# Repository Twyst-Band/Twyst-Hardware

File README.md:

# Twyst — Intelligent Motion Tracking & Exercise Feedback System

## Overview

Twyst is a wearable motion analysis system that integrates sensor-embedded bandanas with an intuitive mobile application to monitor, evaluate, and improve human movement. Designed for sports, fitness, rehabilitation, and physical therapy, Twyst provides real-time feedback on exercise execution accuracy using advanced motion analysis and AI-based comparison algorithms.

Developed by students from the National College of Computer Science “Grigore Moisil” Brașov, Twyst combines embedded engineering, data science, and mobile app design to create a seamless hardware-software ecosystem that makes motion tracking accessible and engaging.
 
## Objectives

Twyst aims to:
- Provide precise motion analysis using distributed wearable sensors.
- Deliver live, data-driven feedback for form correction and performance improvement.
- Develop a machine-learning framework that learns from professionals and guides beginners.
- Support medical rehabilitation by tracking therapeutic exercises and preventing re-injury.
- Offer a comfortable, modular, and scalable hardware system adaptable to various body types and activities.

Key operational goals include:
- <2° RMS error in orientation estimation.
- 95% exercise recognition accuracy.
- Real-time posture correction feedback.
- 8+ hours battery life and automatic calibration.

## How It Works

The system operates in two main phases:
1.	Training Phase – A professional user performs multiple repetitions of an exercise wearing several Twyst bandanas. The algorithm identifies the most relevant sensors and stores their motion data as a reference.
2.	User Phase – A beginner attaches bandanas to the same body parts and performs the exercise. Twyst compares their movement to the reference model, scoring accuracy and providing corrective suggestions.

Twyst uses sensor fusion (Kalman filters) to combine gyroscope, accelerometer, and magnetometer data. Movement analysis and comparison are based on Principal Component Analysis (PCA) for segmentation and Bézier curve modeling for motion representation, ensuring precise yet efficient feedback.

## Related Work

Twyst draws inspiration from several existing systems:
- SlimeVR: Open-source IMU-based full-body tracker for VR; lacks exercise integration and suffers from drift.
- OptiTrack: High-precision optical tracking used in professional environments; too costly and complex for personal use.
- Oculus Insight: Inside-out tracking with 6DoF accuracy; limited to upper-body movement and headset constraints.

Twyst bridges the gap — delivering OptiTrack-like accuracy with SlimeVR’s affordability and Oculus’ simplicity, optimized for fitness and rehabilitation.

## Software Architecture

Mobile Application
- Built in SwiftUI (iOS), with an Android version in development.
- Features include:
- Exercise browsing and categorization.
- Live activity tracking and performance analytics.
- Gamified UI inspired by Duolingo, featuring progress visualization, rewards, and motivational feedback.
- Mascot: Twy — a friendly athletic fox serving as a motivational guide and branding symbol.

Embedded Software
- Runs on ESP32-C3 using the Arduino framework (C).
- Handles sensor communication (SPI/I²C), data fusion, calibration, and Bluetooth data transfer.
- Implements local Kalman filtering before aggregating data to the main bandana and mobile app for analysis.

## Hardware Design

Bandana Types
- Main Bandana: Acts as the master node; equipped with a touchscreen, pulse oximeter, and temperature sensor.
- Secondary Bandanas: Smaller, lightweight, and communicate with the main unit via UWB and Bluetooth.

## Components

Component	Model / Description
Microcontroller	ESP32-C3
IMU	MPU9250
UWB Module	Ai-Thinker BU03 DW3000
Display	Waveshare Round TFT (GC9A01 driver)
Pulse Oximeter	GY-MAX30100
Temperature Sensor	MF52
Battery	Li-Po with Boost Regulator HW626
Material	PETG 3D-printed enclosures, nylon straps

## Electronics & Prototyping
- Designed using KiCad for PCB schematics.
- 3D-printed casings optimized for comfort and modular assembly.
- Built for durability, skin safety, and easy debugging.

## Business Model

Twyst’s business strategy focuses on:
- Selling hardware kits (bandanas + mobile app).
- Generating secondary revenue from anonymized motion data used in research, medicine, and biomechanics.
- Promoting accessibility and personalization to encourage wide adoption across fitness, rehabilitation, and research markets.

Business Plan
Research Paper

## Research & Algorithms

Twyst’s research focuses on mathematical modeling for accurate motion comparison:
- Sensor Model: Quaternion-based orientation estimation via Kalman filtering.
- Segmentation: PCA identifies repetitions and removes noise.
- Motion Representation: Bézier curves smooth motion data for scalable comparison.
- Evaluation Metrics: Curve distance, amplitude, and phase alignment define feedback precision.

These techniques ensure low drift, real-time responsiveness, and robust cross-user comparison.

## License

This project is currently in research and prototype stage under educational use. Future licensing will be determined upon commercial release.
 presentation)?

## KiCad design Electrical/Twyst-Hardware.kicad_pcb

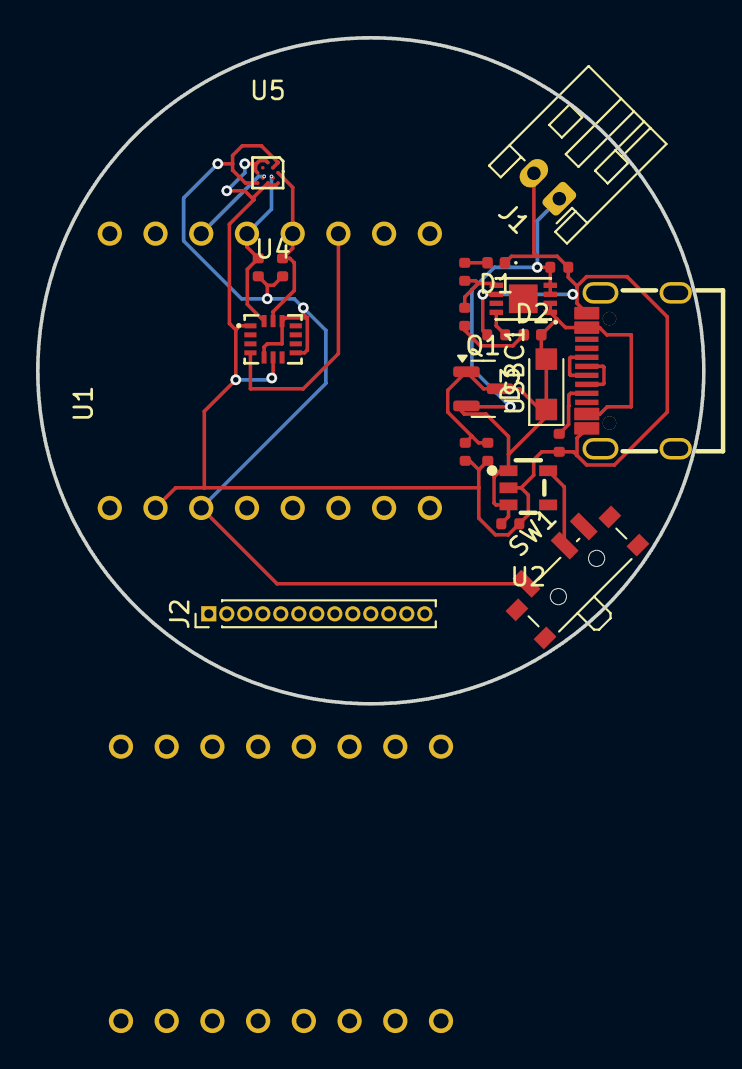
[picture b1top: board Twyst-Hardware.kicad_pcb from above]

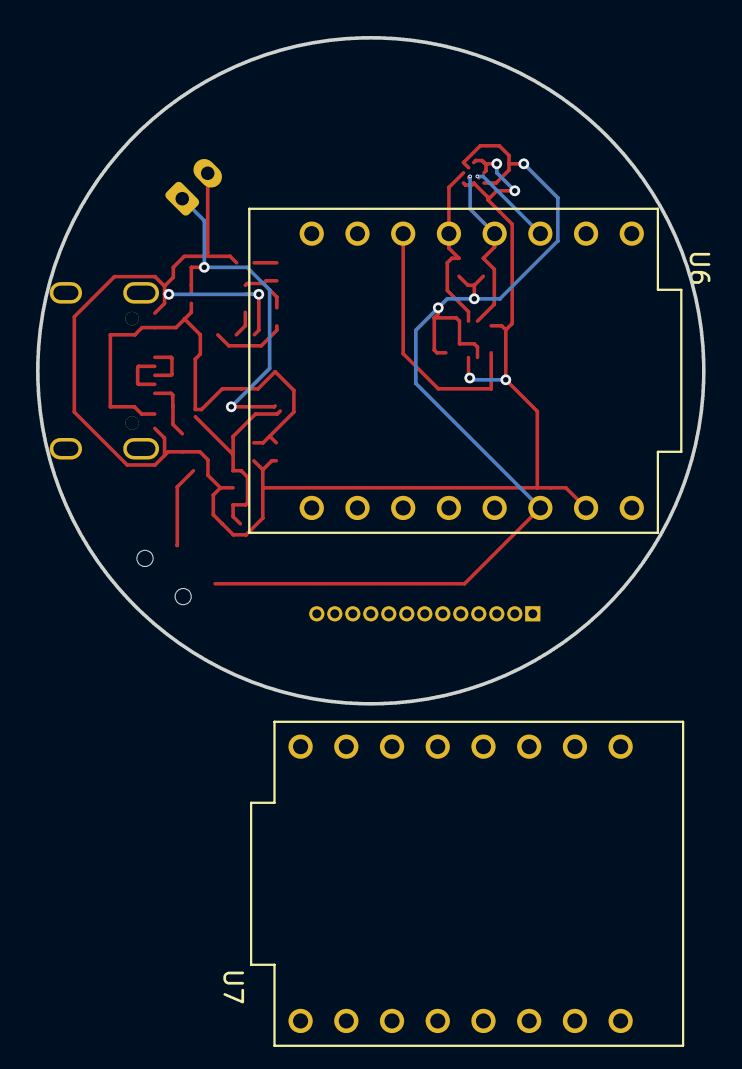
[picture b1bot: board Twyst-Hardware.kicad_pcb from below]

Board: 2 copper layers, 37.0 x 37.0 mm, 24 parts (2 on the bottom side), 17 nets.

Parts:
C1, C2, C3: 10µF; C_0402
D1, D2: LED; LED_0402_1005Metric
D3: PMEG4020ER; Nexperia_CFP3_SOD-123W
J1: Conn_01x02_Pin; JST_PH_S2B-PH-K_1x02_P2.00mm_Horizontal
J2: Conn_01x13_Pin; PinHeader_1x13_P1.00mm_Vertical
Q1: BSS84; SOT-23
R1: 5.1kΩ; R_0402
R2: 2kΩ; R_0402
R3, R4: 1kΩ; R_0402
R5: 100kΩ; R_0402
R6, R7: 4.7kΩ; R_0402
SW1: SW_SPDT; SW_SPDT_PCM12
U1: MCP73831-2ACI/MC; TDFN-8_L3.0-W2.0-P0.50-BL-EP1.6
U2: AP2112K-3.3TRG1_C23380830; SOT-23-5_L2.9-W1.6-P0.95-LS2.8-BR
U4: ICM-45686; LGA-14_L3.0-W2.5-P0.50-TL
U5: BMM150; WLCSP-12_L1.6-W1.6_BMM150
U6, U7: ESP32-C3_SUPERMINI_TH; MODULE_ESP32-C3_SUPERMINI_TH
USBC1: TYPE-C-31-M-12; USB-C_SMD-TYPE-C-31-M-12_1

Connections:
+3.3V: R6.1, R7.1, SW1.1 (A), U4.5 (VDDIO), U4.8 (VDD), U4.12 (AP_CS), U5.A1 (PS), U5.B2 (VDDIO), U5.E5 (VDD), U6.3.3 (3V3), U7.3.3 (3V3)
D+: USBC1.A7 (DN1), USBC1.B7 (DN2)
D-: USBC1.A6 (DP1), USBC1.B6 (DP2)
GND: C1.1, C2.2, C3.2, D1.1 (K), J1.2, R1.1, R2.2, R5.2, U1.6 (VSS), U2.2 (GND), U4.1 (AP_SDO/AP_AD0), U4.6 (GND), U5.A5 (CSB), U5.C1 (SDO), U5.C5 (GND), U5.E1 (GND), U5.E3 (GND), U6.G (GND), U7.G (GND), USBC1.A1B12 (GND), USBC1.B1A12 (GND)
unnamed: D1.2 (A), R4.1
unnamed: D2.1 (K), R3.1
unnamed: SW1.2 (B), U2.5 (VOUT)
unnamed: R2.1, U1.8 (PROG)
unnamed: R3.2, R4.2, U1.5 (STAT)
unnamed: R7.2, U4.13 (AP_SCL/AP_SCLK), U5.A3 (SCK), U6.9 (GPIO9)
unnamed: R6.2, U4.14 (AP_SDA/AP_SDIO/AP_SDI), U5.B4 (SDI), U6.8 (GPIO8)
unnamed: U4.4 (INT1/INT), U6.10 (GPIO10)
unnamed: U5.D4 (DRY), U6.7 (GPIO7)
unnamed: R1.2, USBC1.A5 (CC1)
VBAT: C2.1, J1.1, Q1.3 (D), U1.3 (VBAT), U1.4 (VBAT)
VBUS: C1.2, D2.2 (A), D3.2 (A), Q1.1 (G), R5.1, U1.1 (VDD), U1.2 (VDD), USBC1.A4B9 (VBUS), USBC1.B4A9 (VBUS)
VSH: C3.1, D3.1 (K), Q1.2 (S), U2.1 (VIN), U2.3 (EN)

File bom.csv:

Designator,Footprint,Quantity,Value,LCSC Part #
"C1, C2, C3",C_0402,3,10µF,
"D1, D2",0402,2,LED,
D3,Nexperia_CFP3_SOD-123W,1,PMEG4020ER,
J1,JST_PH_S2B-PH-K_1x02_P2.00mm_Horizontal,1,Conn_01x02_Pin,
Q1,SOT-23,1,BSS84,
R1,R_0402,1,5.1kΩ,
R2,R_0402,1,2kΩ,
"R3, R4",R_0402,2,1kΩ,
R5,R_0402,1,100kΩ,
"R6, R7",R_0402,2,4.7kΩ,
SW1,SW_SPDT_PCM12,1,SW_SPDT,
U1,TDFN-8_L3.0-W2.0-P0.50-BL-EP1.6,1,MCP73831-2ACI/MC,C150772
U2,SOT-23-5_L2.9-W1.6-P0.95-LS2.8-BR,1,AP2112K-3.3TRG1_C23380830,C23380830
U4,LGA-14_L3.0-W2.5-P0.50-TL,1,ICM-45686,C22459454
U5,WLCSP-12_L1.6-W1.6_BMM150,1,BMM150,C171681
U6,MODULE_ESP32-C3_SUPERMINI_TH,1,ESP32-C3_SUPERMINI_TH,
USBC1,USB-C_SMD-TYPE-C-31-M-12_1,1,TYPE-C-31-M-12,C165948
`

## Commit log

2025-10-09 Fixed schematic
2025-10-17 added files
2025-10-21 Added new and improved schematic
2025-10-21 Added new and improved version
2025-10-22 Refactored folder structure
2025-10-22 Added gitignore
2025-10-22 Added screen module in schematics
2025-10-23 Added 3d models
2025-10-23 Added necessary files for blueprint
